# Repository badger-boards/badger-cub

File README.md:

# Badger
An open source E-ink badge that follows you where a badge does.

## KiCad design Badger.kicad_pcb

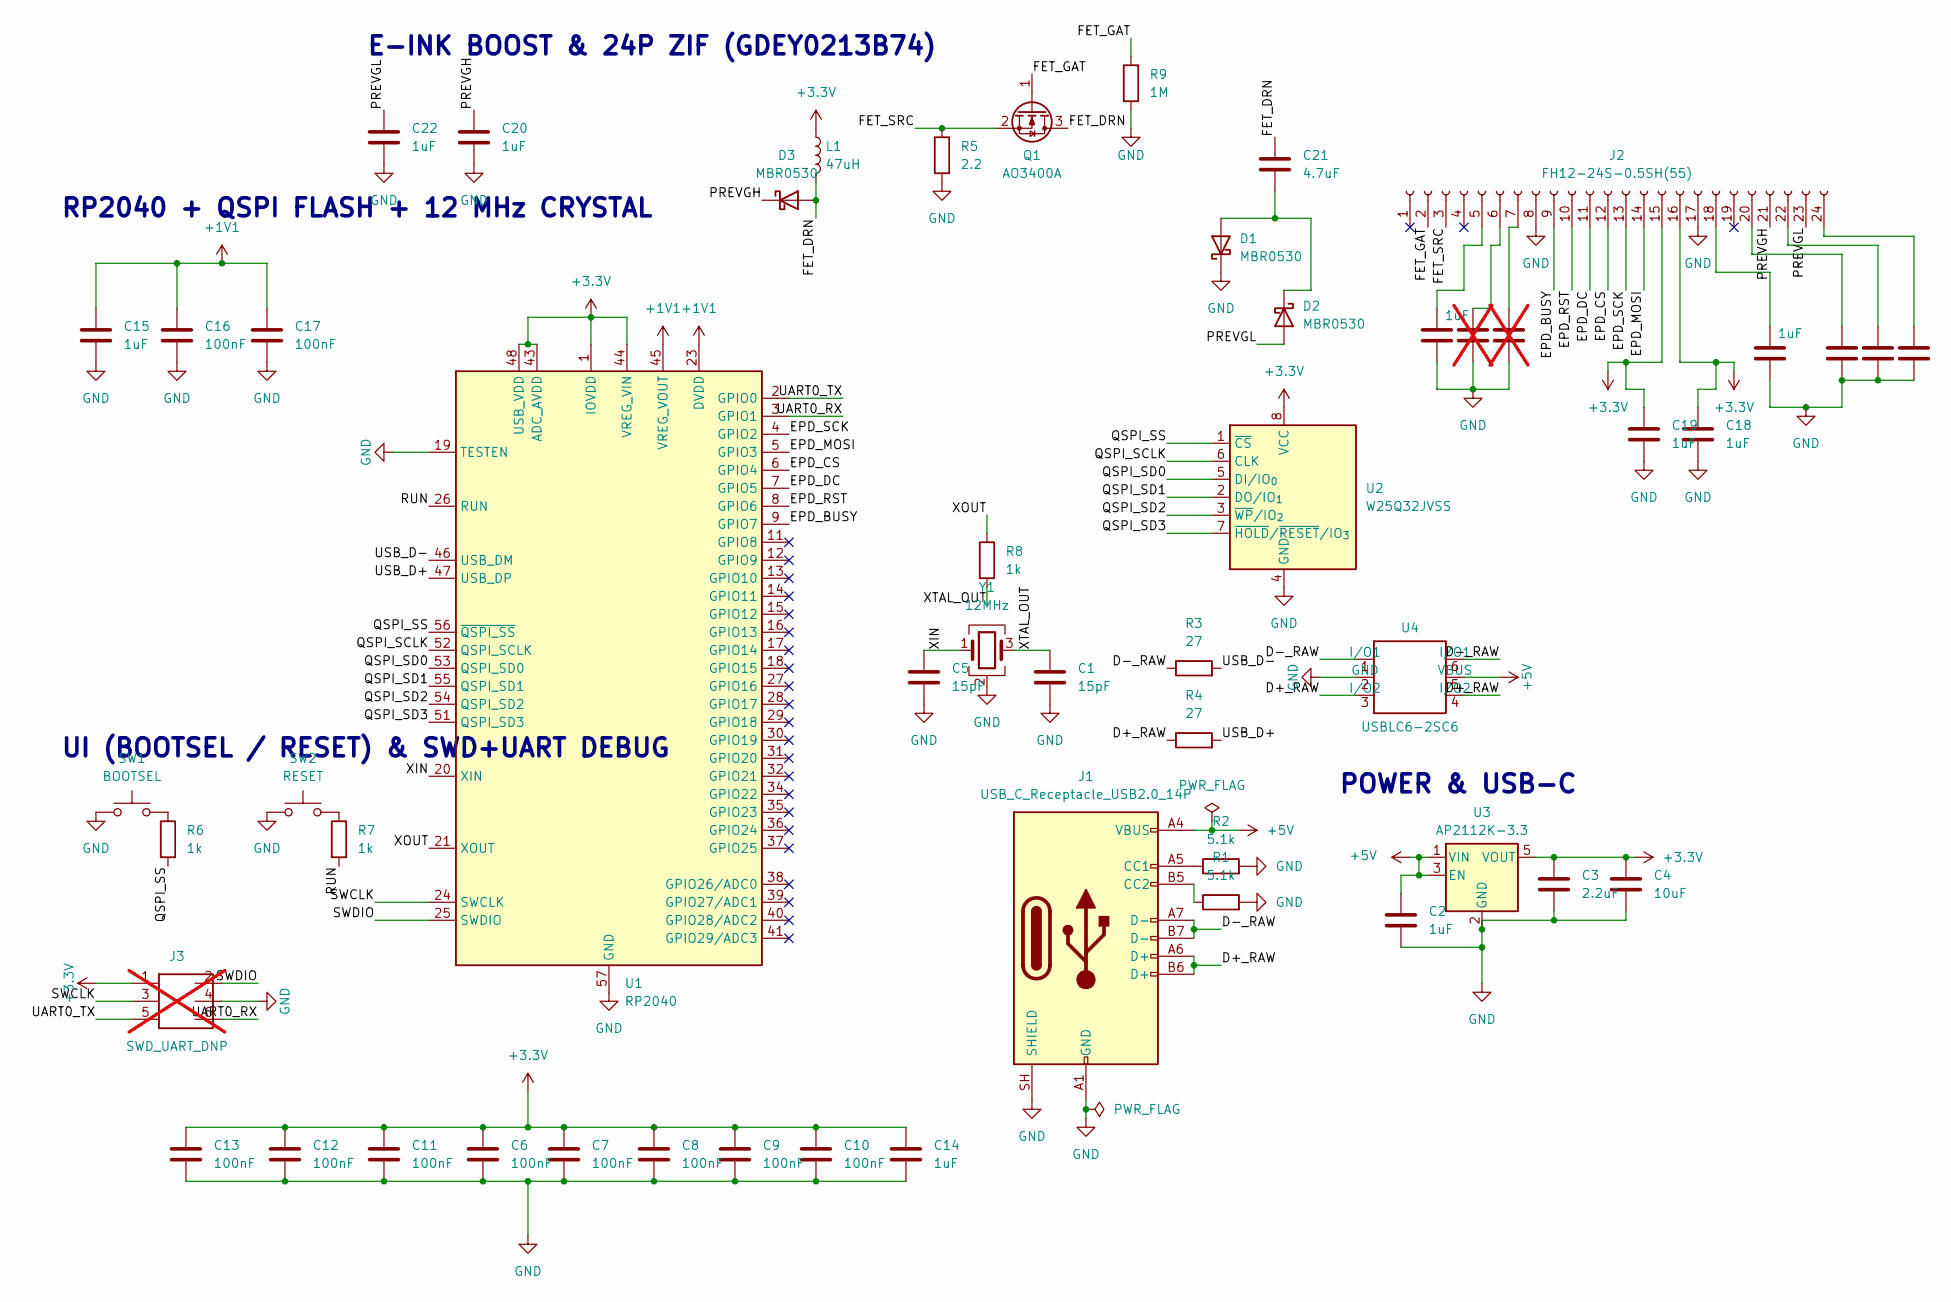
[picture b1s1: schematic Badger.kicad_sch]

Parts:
C1, C5: 15pF; C_0603_1608Metric; MPN CL10C150JB8NNNC; LCSC C1644
C2, C14, C15, C18, C19, C23, C26, C28, C29, C30: 1uF; C_0603_1608Metric; MPN CL10A105KB8NNNC; LCSC C15849
C3: 2.2uF; C_0603_1608Metric; MPN CL10A225KO8NNNC; LCSC C23630
C4: 10uF; C_1206_3216Metric; MPN CL31A106KBHNNNE; LCSC C13585
C6, C7, C8, C9, C10, C11, C12, C13, C16, C17: 100nF; C_0603_1608Metric; MPN CC0603KRX7R9BB104; LCSC C14663
C20, C22: 1uF; C_0603_1608Metric; Voltage 50V; MPN CL10A105KB8NNNC; LCSC C15849
C21: 4.7uF; C_0603_1608Metric; MPN CL10A475KA8NQNC; LCSC C69335
C24, C25: 1uF; C_0603_1608Metric; MPN CL10A105KB8NNNC; LCSC C15849; not fitted
D1, D2, D3: MBR0530; D_SOD-123; MPN MBR0530T1G; LCSC C82046
J1: USB_C_Receptacle_USB2.0_14P; USB_C_Receptacle_HRO_TYPE-C-31-M-12; MPN TYPE-C-31-M-12; LCSC C165948
J2: FH12-24S-0.5SH(55); Hirose_FH12-24S-0.5SH_1x24-1MP_P0.50mm_Horizontal; MPN FH12-24S-0.5SH(55); LCSC C202112
J3: SWD_UART_DNP; Tag-Connect_TC2030-IDC-NL_2x03_P1.27mm_Vertical; not fitted
L1: 47uH; L_Changjiang_FNR4030S; MPN FNR4030S470MT; LCSC C167888
Q1: AO3400A; SOT-23; MPN AO3400A; LCSC C20917
R1, R2: 5.1k; R_0603_1608Metric; MPN 0603WAF5101T5E; LCSC C23186
R3, R4: 27; R_0603_1608Metric; MPN 0603WAF270JT5E; LCSC C25190
R5: 2.2; R_0603_1608Metric; MPN 0603WAF220KT5E; LCSC C22939
R6, R7, R8: 1k; R_0603_1608Metric; MPN 0603WAF1001T5E; LCSC C21190
R9: 1M; R_0603_1608Metric; MPN 0603WAF1004T5E; LCSC C22935
SW1: BOOTSEL; SW_SPST_TL3342; MPN TS-1187A-B-A-B; LCSC C318884
SW2: RESET; SW_SPST_TL3342; MPN TS-1187A-B-A-B; LCSC C318884
U1: RP2040; QFN-56-1EP_7x7mm_P0.4mm_EP3.2x3.2mm; MPN RP2040; LCSC C2040
U2: W25Q32JVSS; SOIC-8_5.3x5.3mm_P1.27mm; MPN W25Q32JVSSIQ; LCSC C179173
U3: AP2112K-3.3; SOT-23-5; MPN AP2112K-3.3TRG1; LCSC C51118
U4: USBLC6-2SC6; SOT-23-6; MPN USBLC6-2SC6; LCSC C7519
Y1: 12MHz; Crystal_SMD_3225-4Pin_3.2x2.5mm; MPN ABM8-272-T3; LCSC C20625731

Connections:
+1V1: C15.1, C16.1, C17.1, U1.23 (DVDD), U1.45 (VREG_VOUT), U1.50 (DVDD)
+3.3V: C3.1, C4.1, C6.1, C7.1, C8.1, C9.1, C10.1, C11.1, C12.1, C13.1, C14.1, C18.1, C19.1, J2.15, J2.16, J3.1, L1.1, U1.1 (IOVDD), U1.10 (IOVDD), U1.22 (IOVDD), U1.33 (IOVDD), U1.42 (IOVDD), U1.43 (ADC_AVDD), U1.44 (VREG_VIN), U1.48 (USB_VDD), U1.49 (IOVDD), U2.8 (VCC), U3.5 (VOUT)
+5V: C2.1, J1.A4 (VBUS), J1.A9 (VBUS), J1.B4 (VBUS), J1.B9 (VBUS), U3.1 (VIN), U3.3 (EN), U4.5 (VBUS)
/D+_RAW: J1.A6 (D+), J1.B6 (D+), R4.1, U4.3 (I/O2), U4.4 (I/O2)
/D-_RAW: J1.A7 (D-), J1.B7 (D-), R3.1, U4.1 (I/O1), U4.6 (I/O1)
/EPD_BUSY: J2.9, U1.9 (GPIO7)
/EPD_CS: J2.12, U1.6 (GPIO4)
/EPD_DC: J2.11, U1.7 (GPIO5)
/EPD_MOSI: J2.14, U1.5 (GPIO3)
/EPD_RST: J2.10, U1.8 (GPIO6)
/EPD_SCK: J2.13, U1.4 (GPIO2)
/FET_DRN: C21.1, D3.2 (A), L1.2, Q1.3 (D)
/FET_GAT: J2.2, Q1.1 (G), R9.1
/FET_SRC: J2.3, Q1.2 (S), R5.1
/PREVGH: C20.1, D3.1 (K), J2.21
/PREVGL: C22.1, D2.2 (A), J2.23
/QSPI_SCLK: U1.52 (QSPI_SCLK), U2.6 (CLK)
/QSPI_SD0: U1.53 (QSPI_SD0), U2.5 (DI/IO_{0})
/QSPI_SD1: U1.55 (QSPI_SD1), U2.2 (DO/IO_{1})
/QSPI_SD2: U1.54 (QSPI_SD2), U2.3 (~WP/IO_{2})
/QSPI_SD3: U1.51 (QSPI_SD3), U2.7 (~HOLD/~RESET/IO_{3})
/QSPI_SS: R6.2, U1.56 (~QSPI_SS), U2.1 (~CS)
/RUN: R7.2, U1.26 (RUN)
/SWCLK: J3.3, U1.24 (SWCLK)
/SWDIO: J3.2, U1.25 (SWDIO)
/UART0_RX: J3.6, U1.3 (GPIO1)
/UART0_TX: J3.5, U1.2 (GPIO0)
/USB_D+: R4.2, U1.47 (USB_DP)
/USB_D-: R3.2, U1.46 (USB_DM)
/XIN: C5.1, U1.20 (XIN), Y1.1
/XOUT: R8.1, U1.21 (XOUT)
/XTAL_OUT: C1.1, R8.2, Y1.3
GND: C1.2, C2.2, C3.2, C4.2, C5.2, C6.2, C7.2, C8.2, C9.2, C10.2, C11.2, C12.2, C13.2, C14.2, C15.2, C16.2, C17.2, C18.2, C19.2, C20.2, C22.2, C23.2, C24.2, C25.2, C26.2, C28.2, C29.2, C30.2, D1.1 (K), J1.A1 (GND), J1.A12 (GND), J1.B1 (GND), J1.B12 (GND), J1.SH (SHIELD), J2.8, J2.17, J3.4, R1.2, R2.2, R5.2, R9.2, SW1.1, SW2.1, U1.19 (TESTEN), U1.57 (GND), U2.4 (GND), U3.2 (GND), U4.2 (GND), Y1.2 (G), Y1.4 (G)
unnamed: C21.2, D1.2 (A), D2.1 (K)
unnamed: J1.A5 (CC1), R2.1
unnamed: J1.B5 (CC2), R1.1
unnamed: C23.1, J2.5
unnamed: C24.1, J2.6
unnamed: C25.1, J2.7
unnamed: C26.1, J2.18
unnamed: C28.1, J2.20
unnamed: C29.1, J2.22
unnamed: C30.1, J2.24
unnamed: R6.1, SW1.2
unnamed: R7.1, SW2.2

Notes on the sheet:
UI (BOOTSEL / RESET) & SWD+UART DEBUG
RP2040 + QSPI FLASH + 12 MHz CRYSTAL
E-INK BOOST & 24P ZIF (GDEY0213B74)
POWER & USB-C

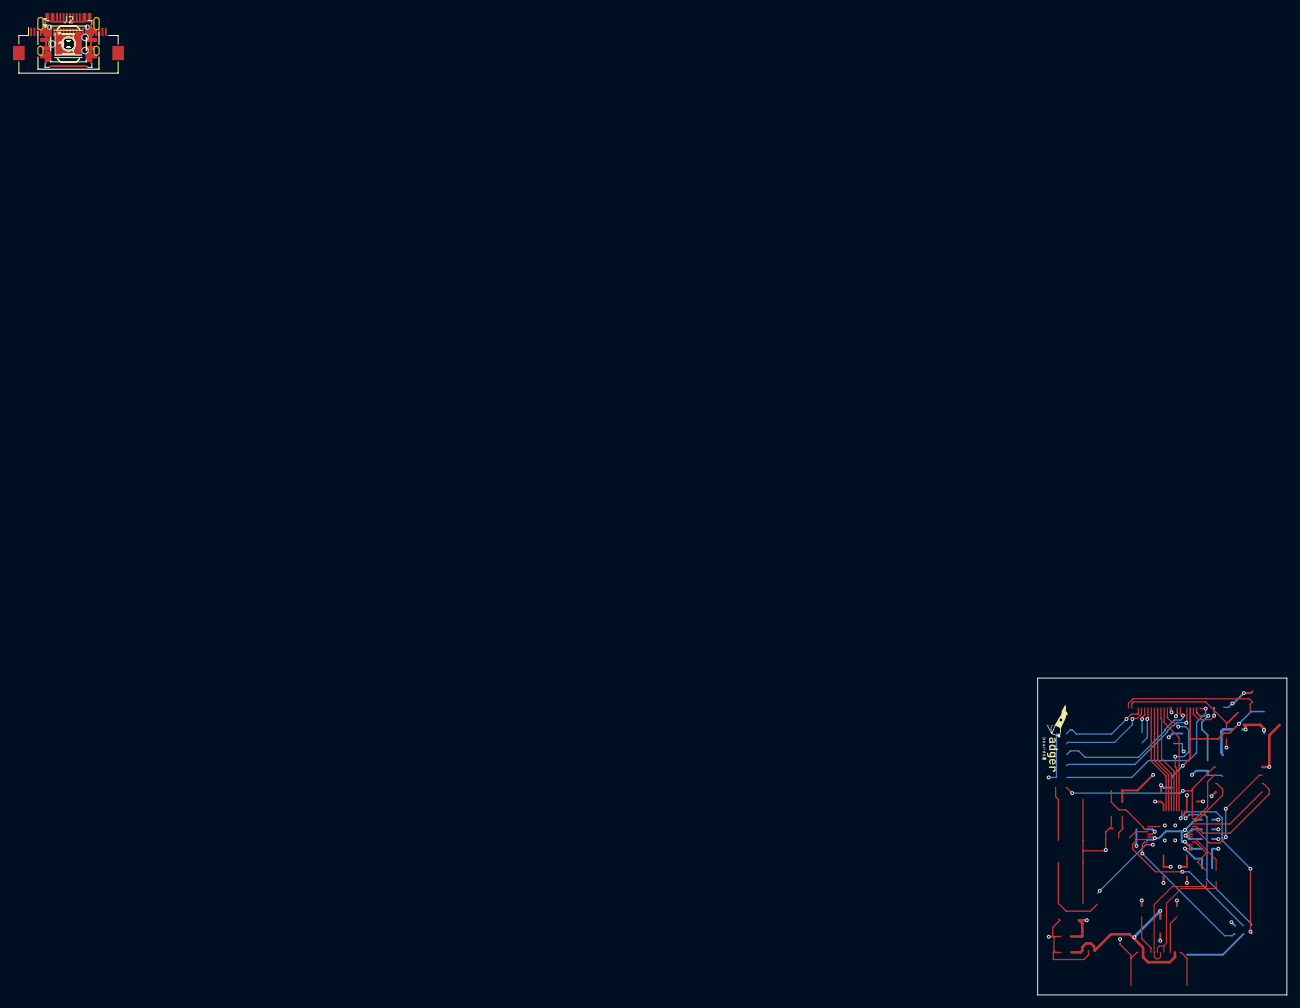
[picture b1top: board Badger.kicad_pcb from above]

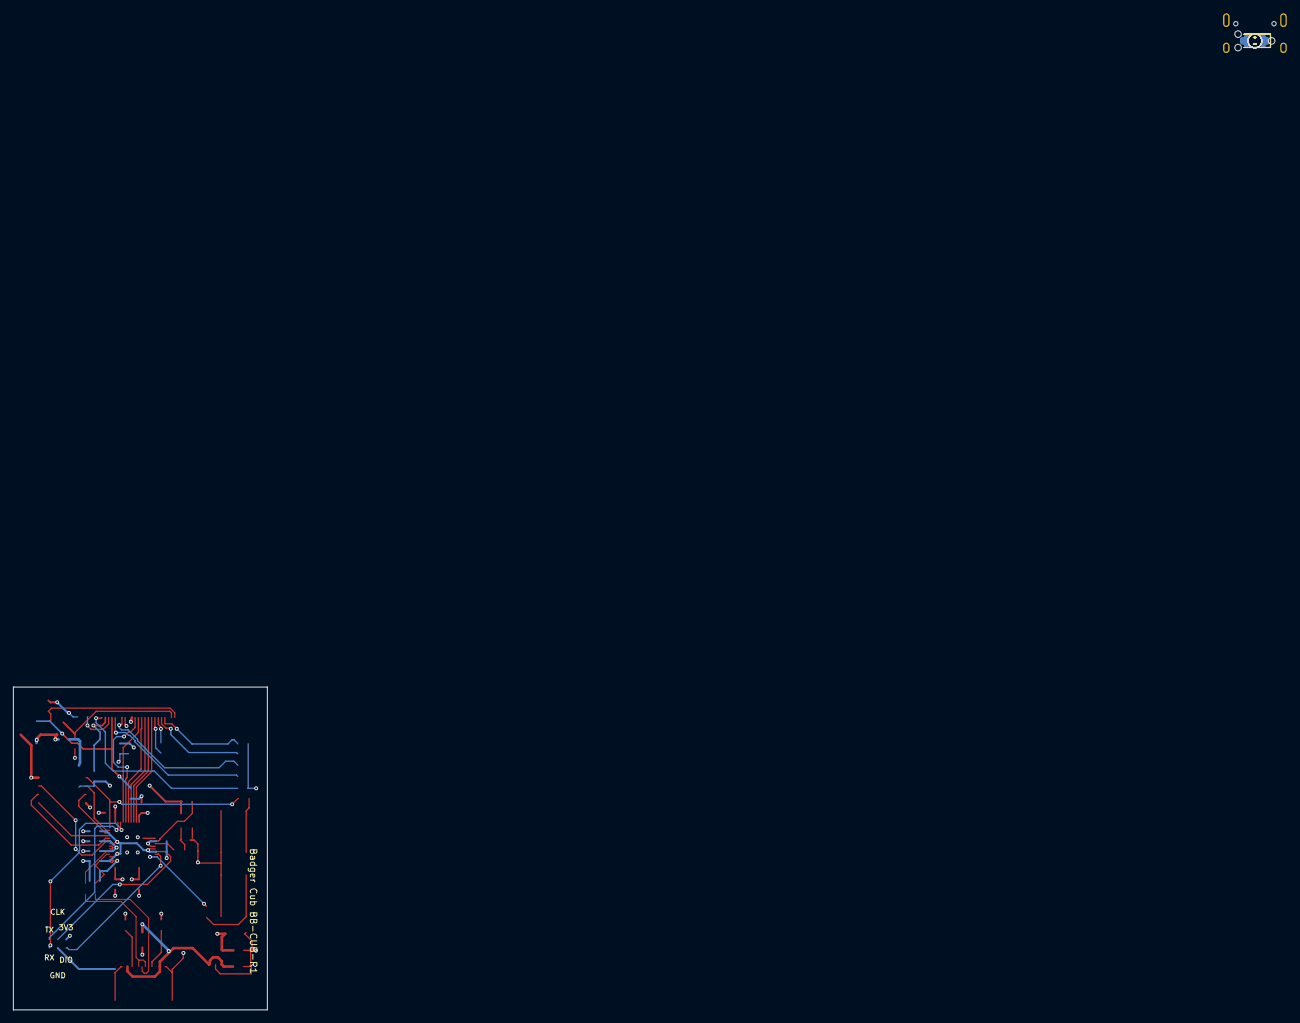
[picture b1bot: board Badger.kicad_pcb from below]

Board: 4 copper layers, 38.4 x 48.8 mm, 57 parts (24 on the bottom side), 45 nets.

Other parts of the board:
H1, H2, H3, H4: MountingHole_2.1mm

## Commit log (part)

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2025-12-02 (chore) initial commit: license, readme, gitignore, internal notes
